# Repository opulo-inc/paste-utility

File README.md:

# [LumenPnP Paste Utility](https://paste.opulo.io/)

The LumenPnP Paste Utility is a web tool for generating and sending paste dispensing Gcode to a LumenPnP equipped with a Paste Extruder Toolhead.

Designed to work with
- Angled luer lock syringe tips with presets for: 20, 22, 23, and 25GA tappered nozzles
- PCBs with at least three 1mm diameter circular fiducials

## Running Locally

1. Install [node.js](https://nodejs.org/en/download) so we can use the package manager npm to continue

2. Go to you cloned directory

3. Install vite first with:

`npm install vite`

4. Then start server:

`npm run dev`

## License

The software in this repository is licensed using MPL 2.0. Opulo's logo, branding, and other media is used throughout this project. This is Copyright (c) Opulo and all rights are reserved. You may not distribute derivative works or products bearing the Opulo logo, icon, iconography, or other relevant mark. Derivative works should remove Opulo branding. The name `Opulo` and `LumenPnP` are trademarked, and only to be used by Opulo. Any derivative works should remove both marks.

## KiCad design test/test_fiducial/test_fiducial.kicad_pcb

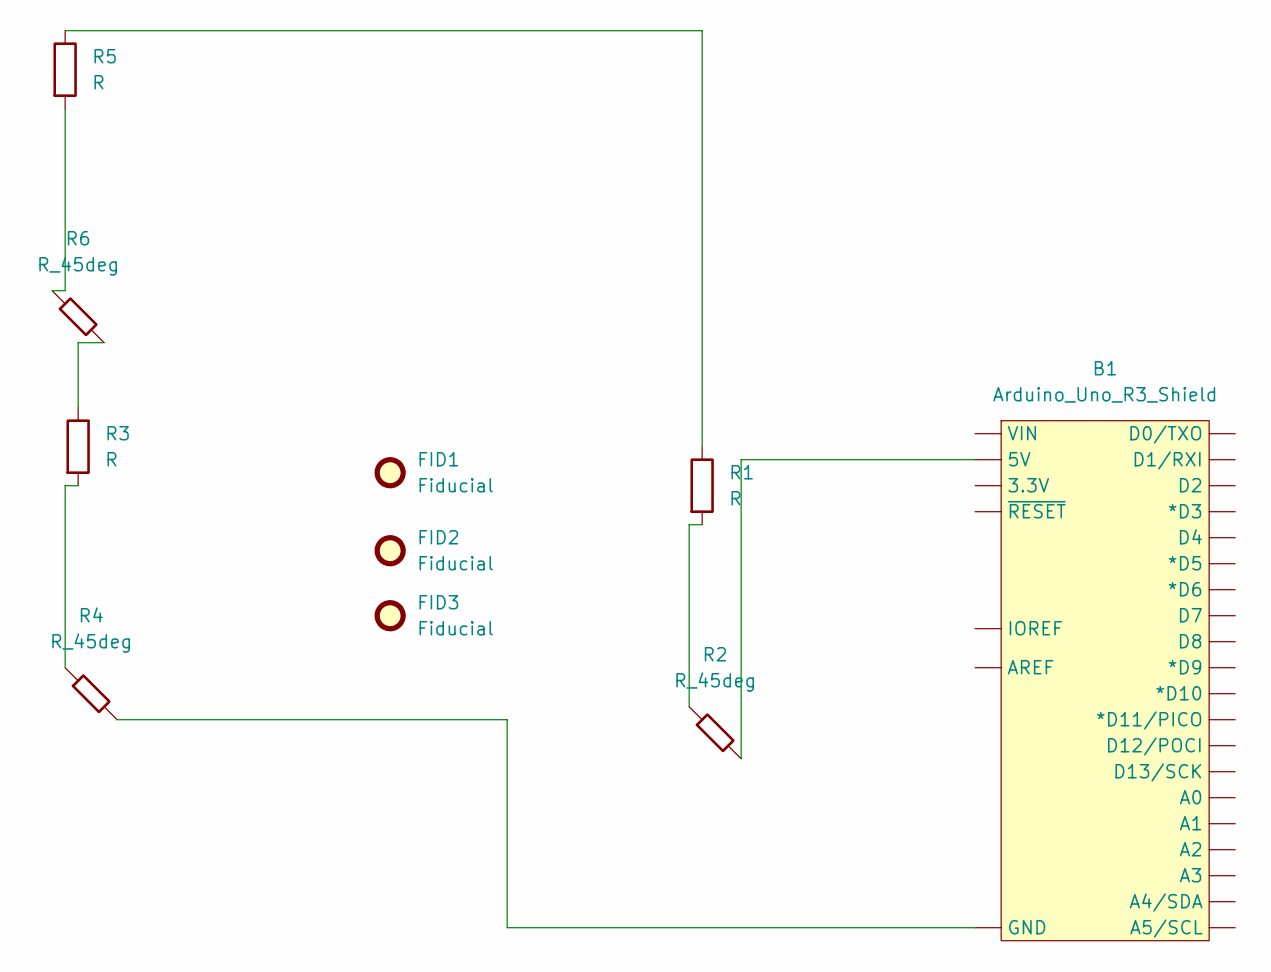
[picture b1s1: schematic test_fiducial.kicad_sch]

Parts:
B1: Arduino_Uno_R3_Shield; Uno_R3_Shield_NoLabels
FID1, FID2, FID3: Fiducial
R1: R; R_0805_2012Metric
R2, R4: R_45deg; R_0805_2012Metric
R3: R; R_0603_1608Metric
R5: R; R_0402_1005Metric
R6: R_45deg; R_0201_0603Metric

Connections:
unnamed: B1.5V, R2.2
unnamed: B1.GND, R4.2
unnamed: R1.1, R5.1
unnamed: R1.2, R2.1
unnamed: R3.1, R6.2
unnamed: R3.2, R4.1
unnamed: R5.2, R6.1

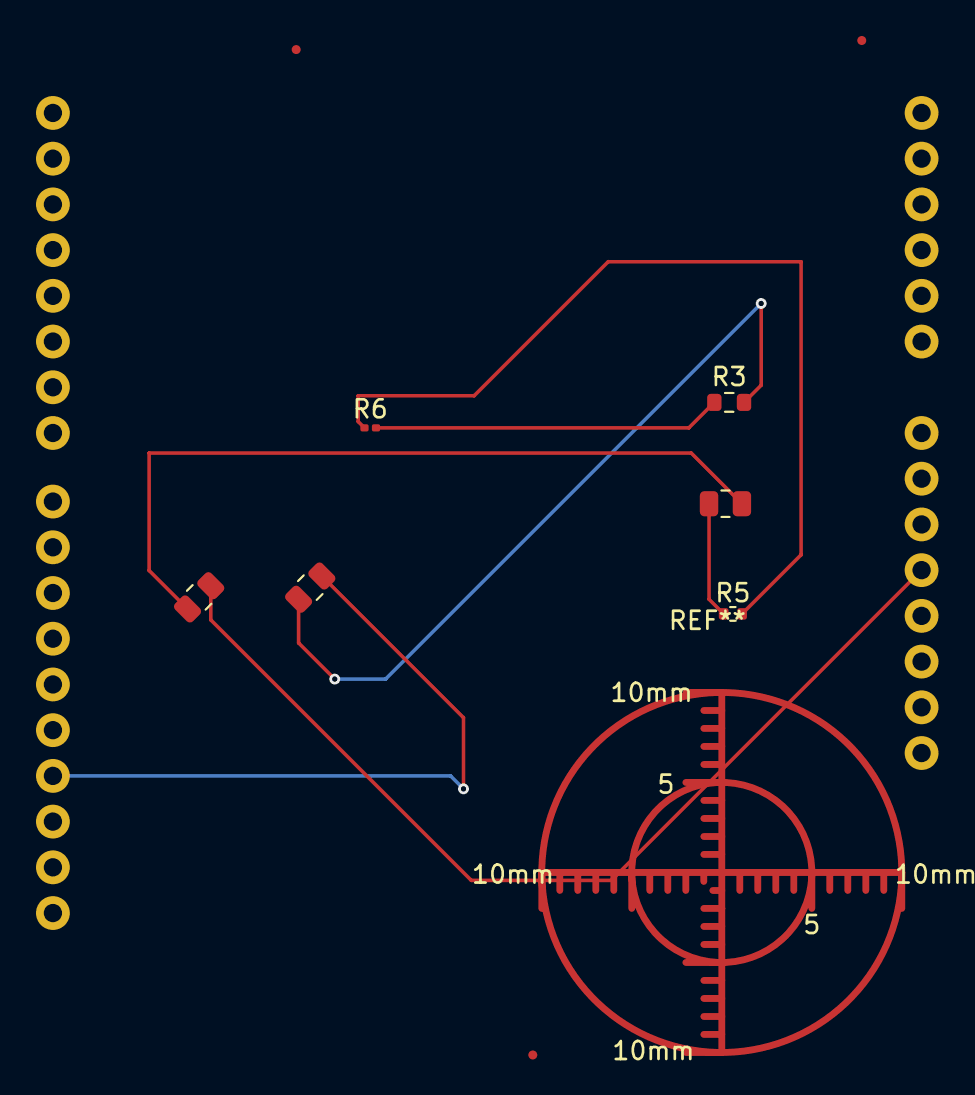
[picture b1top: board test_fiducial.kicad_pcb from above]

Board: 2 copper layers, 10 parts (0 on the bottom side), 7 nets.

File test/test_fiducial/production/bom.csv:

Designator,Footprint,Quantity,Value,LCSC Part #
B1,Uno_R3_Shield_NoLabels,1,Arduino_Uno_R3_Shield,
R1,0805,1,R,
"R2, R4",0805,2,R_45deg,
R3,0603,1,R,
R5,0402,1,R,
R6,0201,1,R_45deg,

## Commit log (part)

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2025-02-13 huge commit, got serial communication working much better, relies on hearing an ok back before sending another, along with a timeout that gets reset when it's busy
2025-02-13 ok, fixed sending, and waiting for ok to continue
2025-02-13 first push up
2025-02-13 deploy: a0d72aa04c3b1688035e25c41f002a69b26ccfeb
2025-02-13 cleans it up a bit, adds jog instructions
2025-02-13 deploy: 53f5a9bc510d0b6b387f907452d6ab4b684fd572
2025-02-14 adds jogging pendant, speed control, and overflow of divs that get filled by js
2025-02-14 deploy: c6899d7aaea5492e68f8314521030789c2212f60
2025-02-14 adds dispense jog buttons
2025-02-14 deploy: fed36f6a2ec968dfd6f54913a3c4c33233640bd1
2025-02-27 adds preliminary gerber processing, breaks slicing and gerber management out into separate classes and files
2025-02-27 deploy: 35d9f0df58e9e5ddd1449dde5695948d4b18dc57
2025-02-27 typos
2025-02-27 deploy: 151bf6322127d5500bdc5c6974a3b0bf5631b930
2025-02-28 fixes bad rendering on large monitors
2025-02-28 deploy: aa00561ae5996ae288ae7ff76cd5227fcb5d92ad
2025-05-21 lotsa updates, getting camera feed in there with opencv functionality
2025-05-21 adds click to jog, cleans up ui a bit
2025-05-28 adds fid scanning, jog to fid
2025-05-29 good clean version iwth fid scanning, pretty decent object model. about to dive into all the gerber stuff
2025-07-26 updates gitignore
2025-07-26 tweaks and updates for gerber support
2025-07-26 deploy: 402d35e200d7eb1001e795bdd8209d2512f11d50
2025-07-26 trying to fix some vite stuff
2025-07-26 more vite tweaks
2025-07-26 deploy: ac3ca569fc9ad97d7d7d60e4107cc10580b61225
2025-07-26 trying to get help.html to be included
2025-07-26 adding help.html to build
2025-07-26 deploy: 62ee0dc06c51e12d7cda59a25bd28d5506d275ca
2025-08-24 added Prusa VenderId
2025-08-24 Added Console to video manager to help debug camera issues
2025-08-25 updates final position after job to move to front corner
2025-08-25 deploy: b280a54d24c32fe1dbcb0a66fe7060c24b9d1b94
2025-09-01 Add Endoscope
2025-09-01 Add more file extensions to Gerber upload functions
2025-09-02 Add Auto Fiducial finder
2025-09-02 updates park position when job is cancelled to 5 5
2025-09-02 deploy: 6cef90bff2a65edb2de0392b79433ff713678480
2025-09-06 Change GCODE to work with PRUSA I3
2025-09-25 vite.config.js edited to run on Github.io
    vite.config.js edited to run on Github.io
2025-09-25 Update deploy.yml
    Install dependencies
2025-09-25 Update package.json add gh-pages
    Update package.json add gh-pages
2025-10-06 Add support for additional Gerber file extensions in file picker
    Extended the file picker to accept paste-specific extensions (.gbp, .gtp) for paste Gerber files and mask-specific extensions (.gbs, .gts) for mask Gerber files, in addition to the standard .gbr exte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
2025-11-08 Add support for Gerber unit and coordinate format commands, support implied moves
2025-11-08 Remove temporary fix
2025-11-12 Improve video acqusition of fiducials
2025-11-13 deploy: 718cd3862d194263dd447bb0a735e30bfa88d8ef
2026-01-08 adds three new settings: pre and post gcode, along with an invert dispense command
2026-01-08 deploy: 06bce4c13f34122b46b70fadb7fbeb1b543f55bd
2026-03-31 deploy: 56c091d058915a91b1b1ed3fb917af7484d781b4
